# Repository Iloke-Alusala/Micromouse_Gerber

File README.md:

# 🐭 Micromouse Power Subsystem – UCT EEE3088F Design Project

This repository contains the KiCad schematic and PCB design files for the **power subsystem** of a modular micromouse robot, developed as part of the EEE3088F final year design course at the University of Cape Town.

---
# ⚠️ Warning: Do Not Use As-Is
This repository contains schematic and PCB design files for a micromouse power subsystem. These designs are provided for reference and educational purposes only.

Several components in the schematic and PCB do not function as intended due to design or implementation limitations, though many of the core design choices and ideas remain valid. Always check all datasheets of ICs and components used in a given section before adopting this to your own design.**

Therefore, this hardware should not be used as-is for production or critical applications.You are encouraged to use the files for inspiration or as a starting point, but please verify and test all circuits thoroughly before use in any real-world system.
---

## 📌 Project Overview

Micromouse robots are autonomous robots that solve mazes using onboard logic and control systems. This project focused on developing the **power subsystem**, a critical part of the micromouse architecture. The design was constrained by size (82mm x 60mm), budget (R600), and modularity requirements. The subsystem is responsible for:

- Supplying **regulated voltages** from the LiPo battery (3.3V and 5V)
- Enabling **bidirectional motor control**
- Charging a **single-cell LiPo battery** (200mA/600mA modes) from Type-C charging
- Providing **external load switching** for sensors and logic
- Supporting **testability** and **fault isolation**

---

## 🔧 Key Design Goals

- **Bidirectional Motor Driving** via dual DRV8833 H-Bridge ICs
- **Type C Battery Charging Support** using TP4056-MS and XL1509 buck converter, as well as the CH224K PD negotiator
- **High-Side Load Switching** through AP22966 ICs (1A per channel)
- **Modular Power Path** allowing buck and charger stages to be tested independently
- **Design-for-Testability** with test points, jumper-control pads, and 1206 resistor footprints
- **Battery Monitoring** using INA219 and I2C connection to external microcontroller
- **Regulated 5V and 3.3V ouptu voltages supporting 300mA and 1.5A outputs**
- **Physical ON-OFF switch for disabling and enabling battery connection to the board**

---

## 📁 Repository Structure
```bash
Micromouse_Power_Subsystem/
├── KiCad_Project/
├── power_subsystem.kicad_sch        # Schematic file
│  ├── power_subsystem.kicad_pcb        # PCB layout
│   ├── project.kicad_pro                # KiCad project file
│   └── gerber/                          # Output Gerber files
├── README.md
##

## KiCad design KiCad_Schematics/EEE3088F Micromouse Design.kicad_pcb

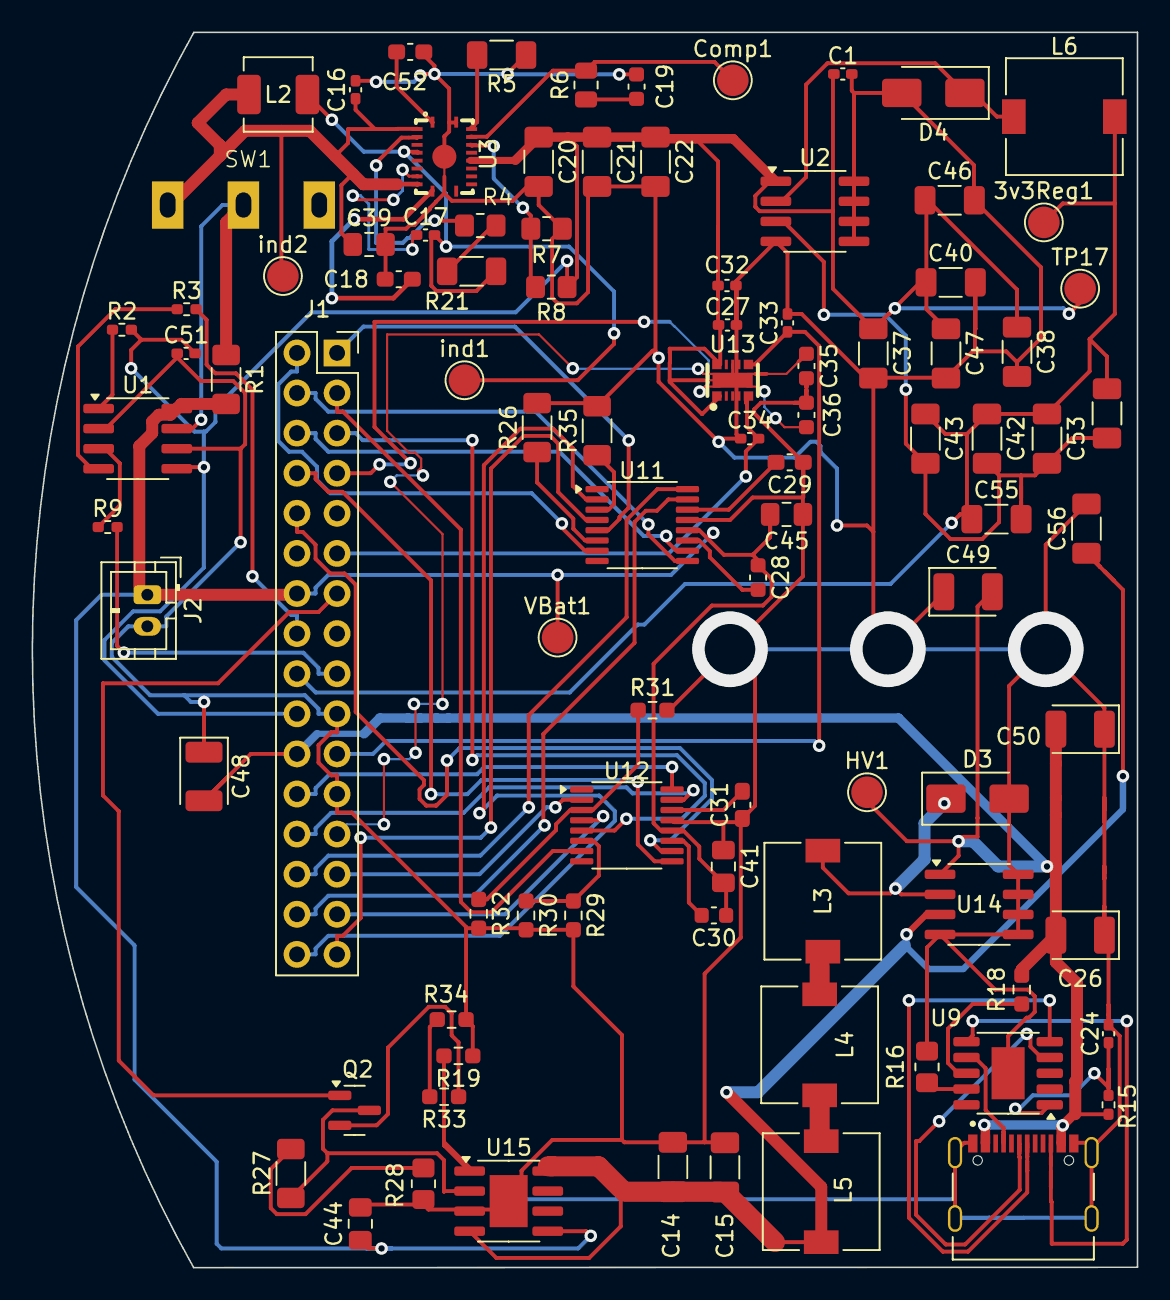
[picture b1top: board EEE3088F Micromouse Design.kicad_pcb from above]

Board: 2 copper layers, 70.0 x 78.3 mm, 94 parts (0 on the bottom side), 71 nets.

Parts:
3v3Reg1: TestPoint; TestPoint_Pad_D2.0mm
C1, C24, C27, C32, C33, C34: 1uF; C_0402_1005Metric_Pad0.74x0.62mm_HandSolder
C14, C15, C42, C43, C47: 47uF; C_1206_3216Metric_Pad1.33x1.80mm_HandSolder
C16, C17, C51: 0.1uF; C_0402_1005Metric_Pad0.74x0.62mm_HandSolder
C18: 47nF; C_0603_1608Metric_Pad1.08x0.95mm_HandSolder
C19, C35, C36: 1nF; C_0603_1608Metric
C20, C21, C22: 22uF; C_1206_3216Metric_Pad1.33x1.80mm_HandSolder
C26, C48, C49, C50: 100uF; CP_EIA-3528-21_Kemet-B
C28, C30: 10nF; C_0603_1608Metric
C29, C31, C52: 2.2uF; C_0603_1608Metric_Pad1.08x0.95mm_HandSolder
C37, C38, C40, C46, C53, C54, C55, C56: 100uF; C_1206_3216Metric_Pad1.33x1.80mm_HandSolder
C39, C41, C44, C45: 10uF; C_0805_2012Metric_Pad1.18x1.45mm_HandSolder
Comp1: TestPoint; TestPoint_Pad_D2.0mm
D3, D4: SS32; D_SMA
HV1: TestPoint; TestPoint_Pad_D2.0mm
J1: Conn_02x16_Odd_Even; PinSocket_2x16_P2.54mm_Vertical
J2: Conn_01x02; JST_PH_B2B-PH-K_1x02_P2.00mm_Vertical
J3: TYPE-C-31-M-12; HRO_TYPE-C-31-M-12
L2: 1.2uH; L_Changjiang_FXL0420
L3, L4, L5, L6: 22uH; L_7.3x7.3_H4.5
Q2: AO3400A; SOT-23
R1: 0.1; R_1206_3216Metric_Pad1.30x1.75mm_HandSolder
R2, R3, R9: 3.3k; R_0402_1005Metric_Pad0.72x0.64mm_HandSolder
R4: 220k; R_0805_2012Metric_Pad1.20x1.40mm_HandSolder
R5: 100k; R_1206_3216Metric_Pad1.30x1.75mm_HandSolder
R6: 68k; R_0805_2012Metric
R7: 47k; R_0805_2012Metric_Pad1.20x1.40mm_HandSolder
R8: 150k; R_0805_2012Metric_Pad1.20x1.40mm_HandSolder
R15: 1k; R_0402_1005Metric_Pad0.72x0.64mm_HandSolder
R16: 6.8k; R_0805_2012Metric_Pad1.20x1.40mm_HandSolder
R18, R19: 10k; R_0603_1608Metric_Pad0.98x0.95mm_HandSolder
R21: 33k; R_1206_3216Metric_Pad1.30x1.75mm_HandSolder
R26, R35: 1; R_1206_3216Metric_Pad1.30x1.75mm_HandSolder
R27: 4.7k; R_1206_3216Metric_Pad1.30x1.75mm_HandSolder
R28: 330; R_0805_2012Metric_Pad1.20x1.40mm_HandSolder
R29, R30, R31, R32: 0.82; R_0603_1608Metric_Pad0.98x0.95mm_HandSolder
R33: 2.2k; R_0603_1608Metric_Pad0.98x0.95mm_HandSolder
R34: 270; R_0603_1608Metric_Pad0.98x0.95mm_HandSolder
SW1: SW_SPDT; SS12D10G4 071
TP17: TestPoint; TestPoint_Pad_D2.0mm
U1: INA219AxD; SOIC-8_3.9x4.9mm_P1.27mm
U2: XL1509-3.3; SOIC-8_3.9x4.9mm_P1.27mm
U3: TPS61088RHLR
U9: CH224K; SSOP-10-1EP_3.9x4.9mm_P1mm_EP2.1x3.3mm
U11, U12: DRV8833PW; TSSOP-16_4.4x5mm_P0.65mm
U13: AP22966DC8-7
U14: XL1509-5.0; SOIC-8_3.9x4.9mm_P1.27mm
U15: TP4056-42-ESOP8; SOIC-8-1EP_3.9x4.9mm_P1.27mm_EP2.41x3.3mm_ThermalVias
VBat1: TestPoint; TestPoint_Pad_D2.0mm
ind1, ind2: TestPoint; TestPoint_Pad_D2.0mm

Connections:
/3.3V Out: 3v3Reg1.1, C42.1, C43.1, C53.1, C54.1, C55.1, J1.18, L6.2
/5V Out: C1.1, C20.1, C21.1, C22.1, C27.1, C32.2, C37.1, C38.1, C40.1, C46.1, C47.1, C51.2, J1.20, R2.2, R8.2, TP17.1, U1.5 (VS), U2.1 (VIN), U3.15 (VOUT_14), U13.4 (VBIAS)
/CTRL_EXT_LOAD1: J1.25, U13.3 (EN1)
/CTRL_EXT_LOAD2: J1.7, U13.5 (EN2)
/EXT_LOAD1_OUT: C33.1, J1.21
/EXT_LOAD2_OUT: C34.2, J1.11
/FAST_CHARGE_CTRL: J1.13, Q2.1 (G)
/FB: R7.2, R8.1, U3.17 (FB)
/HV: C26.2, C48.2, C49.2, C50.2, HV1.1, J1.22, J3.A4_B9 (VBUS), J3.B4_A9 (VBUS), R15.1, R18.2, U14.1 (VIN)
/MOTOR1_A_OUT: J1.32, U11.2 (AOUT1)
/MOTOR1_B_OUT: J1.31, U11.4 (AOUT2)
/MOTOR1_CTRL1: J1.28, U11.16 (AIN1)
/MOTOR1_CTRL2: J1.30, U11.15 (AIN2)
/MOTOR2_CTRL1: J1.4, U11.9 (BIN1)
/MOTOR2_CTRL2: J1.6, U11.10 (BIN2)
/MOTOR3_A_OUT: J1.27, U12.2 (AOUT1)
/MOTOR3_B_OUT: J1.29, U12.4 (AOUT2)
/MOTOR3_CTRL1: J1.24, U12.16 (AIN1)
/MOTOR3_CTRL2: J1.26, U12.15 (AIN2)
/MOTOR4_CTRL1: J1.8, U12.9 (BIN1)
/MOTOR4_CTRL2: J1.10, U12.10 (BIN2)
/Motor2_A_OUT: J1.2, U11.7 (BOUT1)
/Motor2_B_OUT: J1.1, U11.5 (BOUT2)
/Motor4_A_OUT: J1.3, U12.7 (BOUT1)
/Motor4_B_OUT: J1.5, U12.5 (BOUT2)
/SCLK_INA219: J1.16, R3.2
/SDA_INA219: J1.17, R9.2
/Stepped Down 5V: C14.1, C15.1, C56.1, L5.2, U14.3 (FB), U15.4 (V_{CC}), U15.8 (CE)
/V_Battery+: C28.1, C30.1, C41.2, C44.1, C45.2, J1.14, J2.1, R1.2, U1.8 (IN+), U11.12 (VM), U12.12 (VM), U15.5 (BAT), VBat1.1
/Vcc: C16.2, C39.1, L2.1, SW1.1 (A), U3.2 (EN), U3.9 (VIN), ind2.1
GND: C1.2, C14.2, C15.2, C16.1, C18.2, C19.2, C20.2, C21.2, C22.2, C24.2, C26.1, C27.2, C29.1, C31.1, C32.1, C33.2, C34.1, C35.2, C36.2, C37.2, C38.2, C39.2, C40.2, C41.1, C44.2, C45.1, C46.2, C47.2, C48.1, C49.1, C50.1, C51.1, C52.1, C56.2, D3.2 (A), D4.2 (A), J1.19, J1.23, J2.2, J3.A1_B12 (GND), J3.B1_A12 (GND), J3.S1 (SHIELD), J3.S2 (SHIELD), J3.S3 (SHIELD), J3.S4 (SHIELD), R5.1, R7.1, R16.1, R19.1, R26.2, R28.2, R29.2, R30.2, R31.2, R32.2, R34.2, R35.2, U1.2 (A0), U1.6 (GND), U2.4 (~EN), U2.5 (GND), U2.6 (GND), U2.7 (GND), U2.8 (GND), U3.20 (AGND), U3.21 (PGND), U9.11 (GND), U11.13 (GND), U12.13 (GND), U13.11 (GND), U13.15 (EXP), U14.4 (~EN), U14.5 (GND), U14.6 (GND), U14.7 (GND), U14.8 (GND), U15.3 (GND), U15.9 (EPAD)
unnamed: C19.1, R6.1
unnamed: D3.1 (K), L3.1, U14.2 (OUT)
unnamed: D4.1 (K), L6.1, U2.2 (OUT)
unnamed: J3.A5 (CC1), U9.7 (CC1)
unnamed: J3.B5 (CC2), U9.6 (CC2)
unnamed: J3.A7 (DN1), U9.5 (DM)
unnamed: J3.A6 (DP1), U9.4 (DP)
unnamed: L3.2, L4.1
unnamed: L4.2, L5.1
unnamed: Q2.3 (D), R27.1, U15.2 (PROG)
unnamed: Q2.2 (S), R33.1
unnamed: R4.2, R21.2
unnamed: R27.2, R28.1
unnamed: R33.2, R34.1
unnamed: R1.1, SW1.2 (B), U1.7 (IN-)
unnamed: R2.1, U1.1 (A1)
unnamed: R3.1, U1.4 (SCL)
unnamed: R9.1, U1.3 (SDA)
unnamed: C42.2, C43.2, C53.2, C54.2, C55.2, U2.3 (FB)
unnamed: C17.1, U3.8 (BOOT)
unnamed: Comp1.1, R6.2, U3.18 (COMP)
unnamed: R4.1, U3.3 (FSW)
unnamed: R5.2, U3.19 (ILIM)
unnamed: C18.1, U3.10 (SS)
unnamed: C17.2, L2.2, R21.1, U3.5 (SW_4), ind1.1
unnamed: C52.2, U3.1 (VCC)
unnamed: R16.2, U9.9 (CFG1)
unnamed: R18.1, U9.8 (VBUS)
unnamed: C24.1, R15.2, U9.1 (VDD)
unnamed: R35.1, U11.3 (AISEN)
unnamed: R26.1, U11.6 (BISEN)
unnamed: C28.2, U11.11 (VCP)
unnamed: C29.2, U11.14 (VINT)
unnamed: R31.1, R32.1, U12.3 (AISEN)
unnamed: R29.1, R30.1, U12.6 (BISEN)
unnamed: C30.2, U12.11 (VCP)
unnamed: C31.2, U12.14 (VINT)
unnamed: C35.1, U13.12 (SS1)
unnamed: C36.1, U13.10 (SS2)
unnamed: R19.2, U15.1 (TEMP)

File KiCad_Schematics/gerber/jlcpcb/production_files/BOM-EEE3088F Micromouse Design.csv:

Comment,Designator,Footprint,LCSC,Quantity
100uF,C56,C_1206_3216Metric_Pad1.33x1.80mm_HandSolder,C15008,1
10uF,"C41,C44,C45",C_0805_2012Metric_Pad1.18x1.45mm_HandSolder,C15850,3
1nF,"C35,C36",C_0603_1608Metric,C1588,2
10k,R19,R_0603_1608Metric_Pad0.98x0.95mm_HandSolder,C17414,1
330,R28,R_0805_2012Metric_Pad1.20x1.40mm_HandSolder,C17630,1
1,"R26,R35",R_1206_3216Metric_Pad1.30x1.75mm_HandSolder,C17928,2
4.7k,R27,R_1206_3216Metric_Pad1.30x1.75mm_HandSolder,C17936,1
AO3400A,Q2,SOT-23,C20917,1
22uH,"L3,L4,L5",L_7.3x7.3_H4.5,C22463825,3
270,R34,R_0603_1608Metric_Pad0.98x0.95mm_HandSolder,C22966,1
2.2uF,"C29,C31",C_0603_1608Metric_Pad1.08x0.95mm_HandSolder,C23630,2
0.82,"R29,R30,R31,R32",R_0603_1608Metric_Pad0.98x0.95mm_HandSolder,C3013351,4
SS32,D3,D_SMA,C34897,1
2.2k,R33,R_0603_1608Metric_Pad0.98x0.95mm_HandSolder,C4190,1
AP22966DC8-7,U13,AP22966DC8-7,C441830,1
DRV8833PW,"U11,U12",TSSOP-16_4.4x5mm_P0.65mm,C50506,2
1uF,"C1,C27,C32,C33,C34",C_0402_1005Metric_Pad0.74x0.62mm_HandSolder,C52923,5
10nF,"C28,C30",C_0603_1608Metric,C57112,2
XL1509-5.0,U14,SOIC-8_3.9x4.9mm_P1.27mm,C61063,1
100uF,"C26,C48,C49,C50",CP_EIA-3528-21_Kemet-B,C7196,4
TP4056-42-ESOP8,U15,SOIC-8-1EP_3.9x4.9mm_P1.27mm_EP2.41x3.3mm_ThermalVias,C7473158,1
47uF,"C14,C15",C_1206_3216Metric_Pad1.33x1.80mm_HandSolder,C96123,2
Conn_02x16_Odd_Even,,PinSocket_2x16_P2.54mm_Vertical,,0
Conn_01x02,,JST_PH_B2B-PH-K_1x02_P2.00mm_Vertical,,0

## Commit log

2025-03-22 Added KiCad Document files
2025-03-22 Nothing Major
2025-03-22 Added DRV8837 Motor Driver x4. Footprint PCB Organisation outstanding
2025-03-22 Added 3.3V and 5V outputs
2025-03-23 Minor change to voltage regulator
2025-03-23 Added a switch to the battery
2025-03-23 Added USB Type-C Connector
2025-03-23 Added the Battery Charging Circuit
2025-03-24 Added Type-C 9V integration
2025-03-24 Fixed some connector labels
2025-03-24 Redid the Motor circuit with an Improved IC
2025-03-24 Added and fixed the external load switching to an IC instead of discrete components.
2025-03-25 Added 9V -> 5V Buck Converter to feed regulated 5V to Charging IC
2025-03-25 Added parallel resistor combination for 500mA motor. Easier E12 configuration and cheaper
2025-03-25 Added switch changed some stuff to be E12
2025-03-25 Changed Battery Charger to single IC and reformatted components
2025-03-25 Removed the graveyard and restructured board
2025-03-25 Added items to BOM. Need to finish assignment
2025-03-25 Adding JLC part numbers
2025-03-25 Added footprints to 2 of 3 subcircuits
2025-03-25 Added footprints, external load switching is the last circuit that needs labeling and then circuit verification and double checking
2025-03-26 Added footprints for ICs and imported components
2025-03-26 Corrected some footprints and matched LCSC numbers to parts on pcb layout page
2025-03-26 Added more footprints
2025-03-26 Switch time
2025-03-26 Please Read: Replaced buck converter, removed old ones but this has left behind a gap in the copper. The board also needs a curved arc according to Justin. Still need footprints for key ICs, connecto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
2025-03-27 Added footprints for inductors and tantalum capacitors. Also merged buck back to charging IC, and added test points
2025-03-27 Added footprints for inductor, switch and type-c connector
2025-03-27 Fixed the arc to match spec. Added Daniel's components and added all LCSC numbers for them. Fixed the connector footprint, although JST one still needs to be corrected
2025-03-27 Added some text on the silkscreen to delimit the modules
2025-03-27 Found the correct Battery connector
2025-03-27 Added test points and an inductor that was not populated. Added labels
2025-03-27 Found a component that I had not footprinted yet. use the footprint list to check yours please
2025-03-27 Added a bunch of changes
2025-03-27 Updated the INA219 circuit
2025-03-27 First turnover, changed pcb layout
2025-03-27 Fixing errors
2025-03-28 Started routing PCB
2025-03-28 Finishing off
2025-03-28 Finishing off. V2
2025-03-28 Too tired
2025-05-10 Latest force push
2025-05-16 Performing Final Organisation Nuke
2025-05-16 Added Disclaimer and additional design goals.md
2025-05-16 Improved formatting.md
2025-05-16 Further improved formatting.md
